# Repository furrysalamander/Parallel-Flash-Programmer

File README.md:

# Parallel Flash Programmer
 An ATMega based parallel flash programmer.

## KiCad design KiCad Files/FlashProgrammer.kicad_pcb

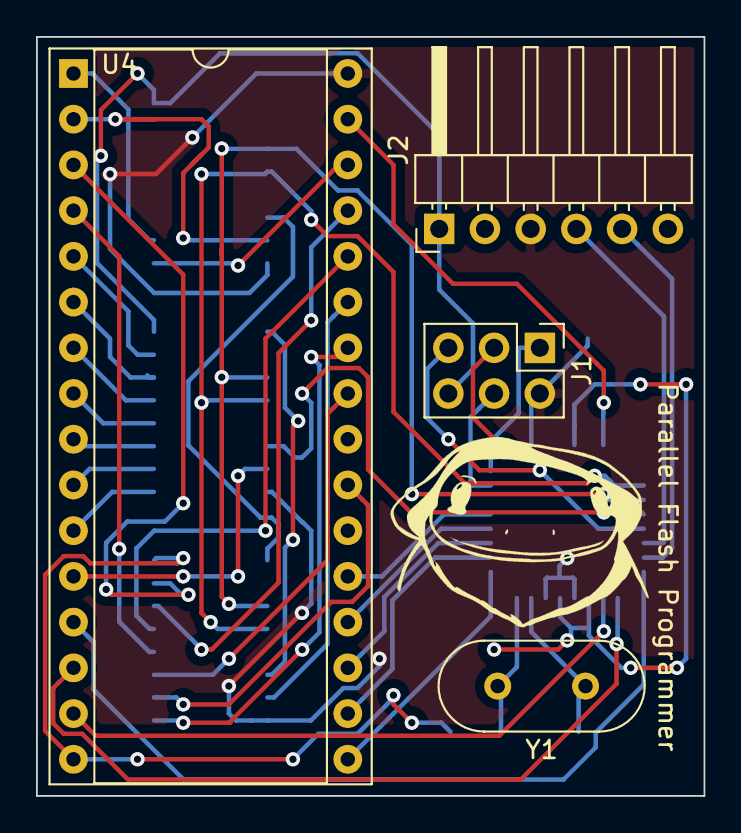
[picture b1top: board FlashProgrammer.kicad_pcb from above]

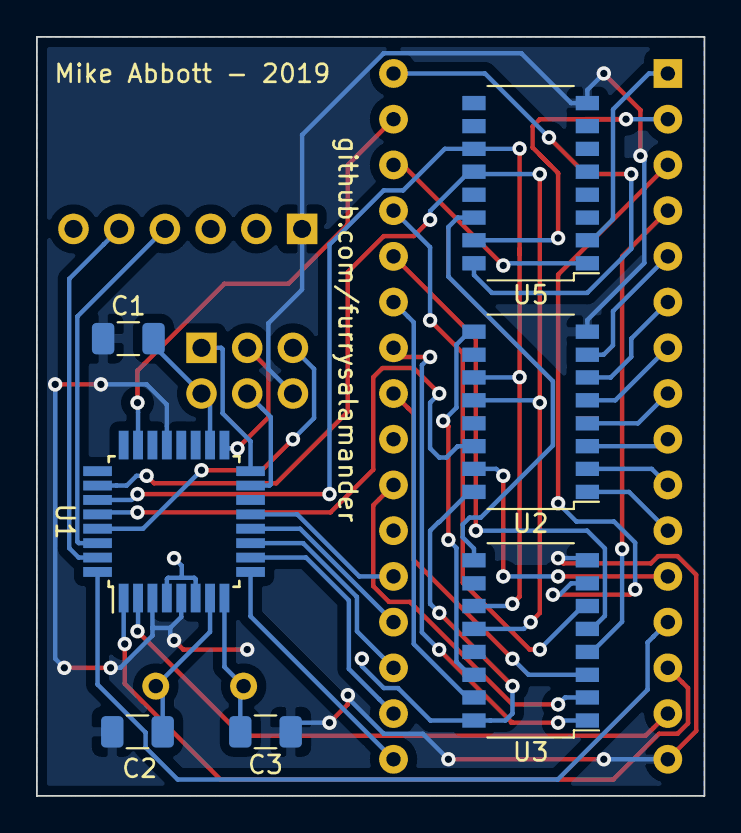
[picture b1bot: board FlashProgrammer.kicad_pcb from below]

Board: 2 copper layers, 37.1 x 42.2 mm, 11 parts (7 on the bottom side), 43 nets.

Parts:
C1: 10uF; C_1206_3216Metric
C2, C3: C_Small; C_1206_3216Metric
J1: ISP Programming Header; PinHeader_2x03_P2.54mm_Vertical
J2: FTDI Cable Header; PinHeader_1x06_P2.54mm_Horizontal
U1: ATmega328P-AU; TQFP-32_7x7mm_P0.8mm
U2, U3, U5: 74HC595; SOP-16_4.4x10.4mm_P1.27mm
U4: SST39SF040; DIP-32_W15.24mm_Socket
Y1: 16MHz; Crystal_HC49-4H_Vertical

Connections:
+5V: C1.2, J1.2, J2.3, U1.4, U1.6, U1.18, U2.16, U3.16, U4.32, U5.16
/Address_0: U2.15, U4.12
/Address_1: U2.1, U4.11
/Address_2: U2.2, U4.10
/Address_3: U2.3, U4.9
/Address_4: U2.4, U4.8
/Address_5: U2.5, U4.7
/Address_6: U2.6, U4.6
/Address_7: U2.7, U4.5
/Address_8: U3.15, U4.27
/Address_9: U3.1, U4.26
/Address_10: U3.2, U4.23
/Address_11: U3.3, U4.25
/Address_12: U3.4, U4.4
/Address_13: U3.5, U4.28
/Address_14: U3.6, U4.29
/Address_15: U3.7, U4.3
/Address_16: U4.2, U5.15
/Address_17: U4.30, U5.1
/Address_18: U4.1, U5.2
/Data_0: U1.32, U4.13
/Data_1: U1.1, U4.14
/Data_2: U1.2, U4.15
/Data_3: U1.9, U4.17
/Data_4: U1.10, U4.18
/Data_5: U1.11, U4.19
/Data_6: U1.12, U4.20
/Data_7: U1.13, U4.21
/MISO: J1.1, U1.16
/MOSI: J1.4, U1.15
/RST: J1.5, U1.29
/RX: J2.4, U1.30
/SCK: J1.3, U1.17
/Shift_Register_Clock_In: U1.26, U2.12, U3.12, U5.12
/Shift_Rollover_0: U2.9, U3.14
/Shift_Rollover_1: U3.9, U5.14
/Shift_Serial_Clock_In: U1.27, U2.11, U3.11, U5.11
/Shift_Serial_In: U1.28, U2.14
/TX: J2.5, U1.31
/Write_Enable: U1.23, U4.31
GND: C1.1, C2.1, C3.1, J1.6, J2.1, U1.3, U1.5, U1.21, U2.8, U3.8, U4.16, U5.8
unnamed: C2.2, U1.7, Y1.1
unnamed: C3.2, U1.8, Y1.2

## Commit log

2019-12-02 initial push
2019-12-02 Added board renders
